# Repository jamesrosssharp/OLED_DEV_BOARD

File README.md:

OLED DEV BOARD
==============

A simple dev board to break out an OLED, PWM sound, buttons, PSRAM
and QSPI flash for making games with iCE40 development boards

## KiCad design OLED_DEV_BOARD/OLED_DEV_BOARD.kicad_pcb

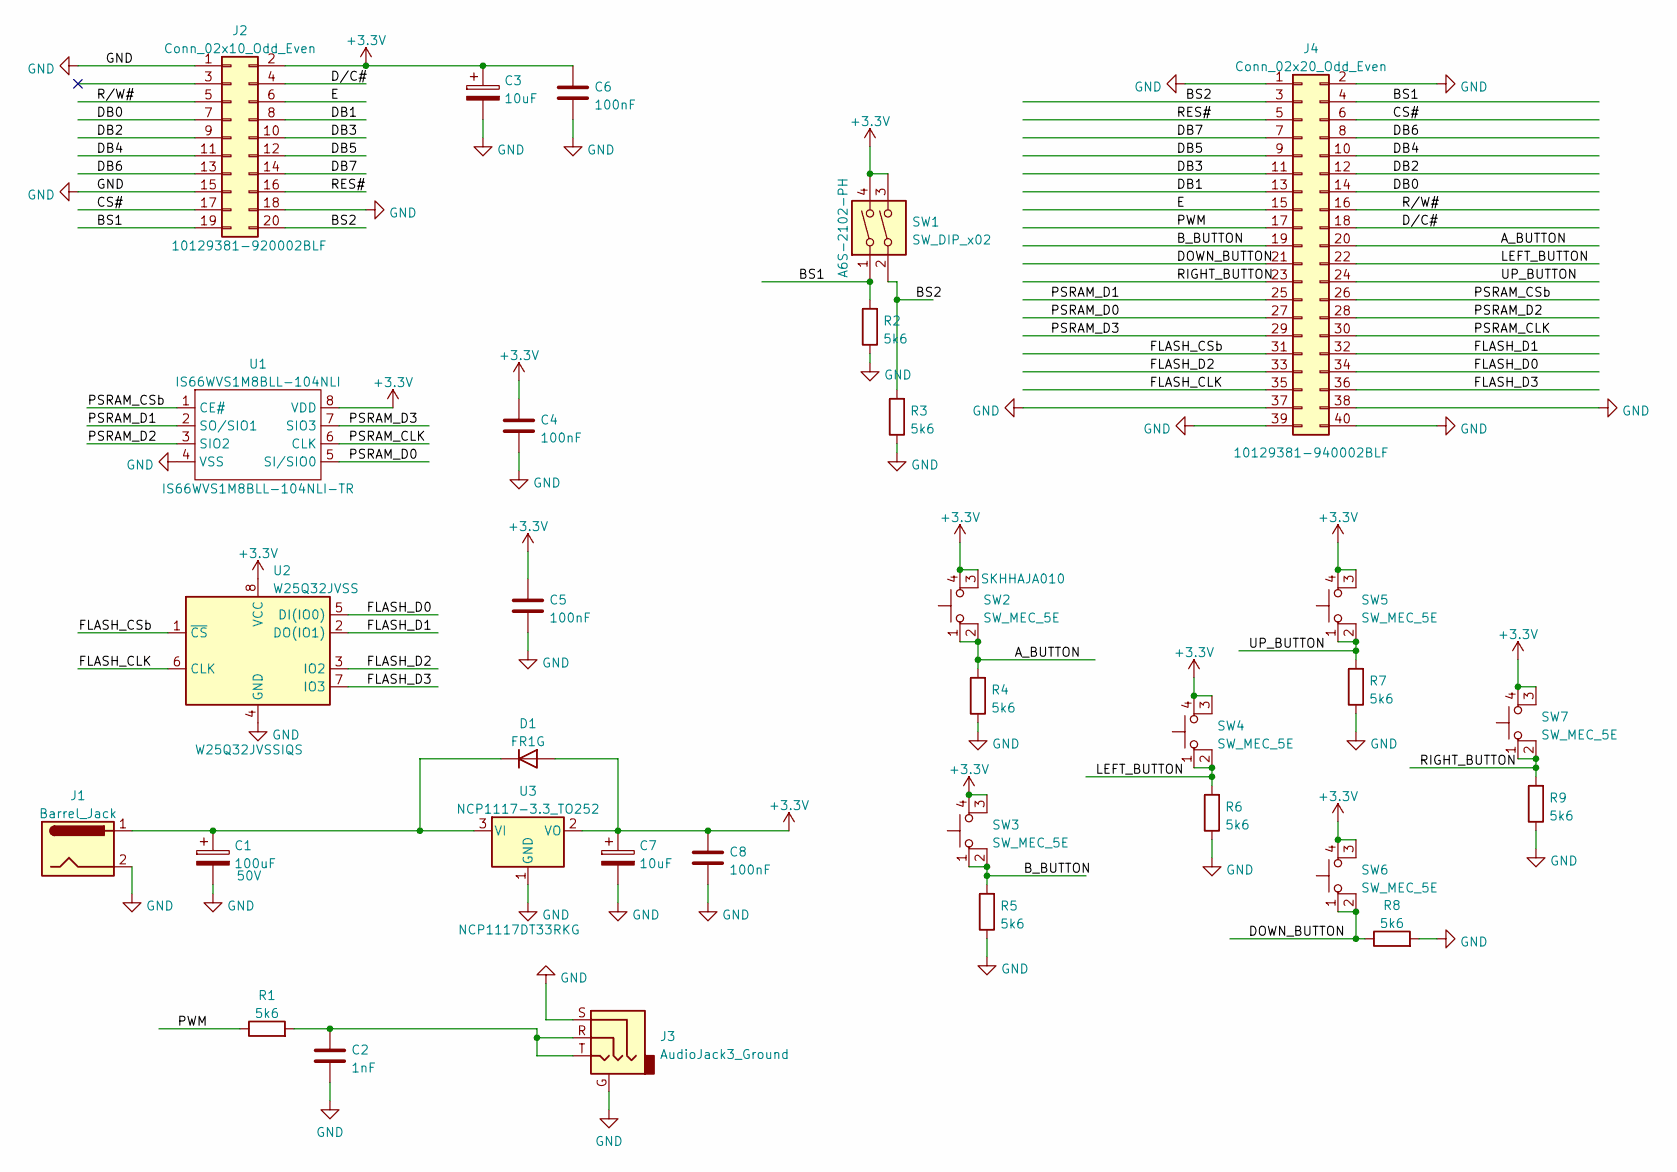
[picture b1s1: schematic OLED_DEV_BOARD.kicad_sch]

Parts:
C1: 100uF; CP_Elec_10x10; Voltage 50V; Manufacturer Part Number GXC1H101MCQ1GS; Mouser Part Number 647-GXC1H101MCQ1GS
C2: 1nF; C_0603_1608Metric; Manufacturer Part Number C0603C102K4RAC7411; Mouser Part Number 80-C0603C102K4RACLR
C3, C7: 10uF; C_1206_3216Metric; Manufacturer Part Number CL31B106KQHNFNE; Mouser Part Number 187-CL31B106KQHNFNE
C4, C5, C6, C8: 100nF; C_0603_1608Metric; Manufacturer Part Number C0603C104K4RACTU; Mouser Part Number 80-C0603C104K4R
D1: FR1G; D_DO-41_SOD81_P10.16mm_Horizontal; Manufacturer Part Number FR1G; Mouser Part Number 637-FR1G
J1: Barrel_Jack; BarrelJack_CUI_PJ-102AH_Horizontal; Manufacturer Part Number PJ-102AH; Mouser Part Number 490-PJ-102AH
J2: Conn_02x10_Odd_Even; NHD-1.8-160128UBC3; Mouser Part Number 649-1012938192002BLF
J3: AudioJack3_Ground; Jack_3.5mm_CUI_SJ-3523-SMT_Horizontal; MPN SJ-3523-SMT-TR; Mouser Part Number 490-SJ-3523-SMT-TR
J4: Conn_02x20_Odd_Even; PinHeader_2x20_P2.54mm_Vertical; Manufacturer Part Number 10129381-940002BLF; Mouser Part Number 649-1012938194002BLF
R1, R2, R3, R4, R5, R6, R7, R8, R9: 5k6; R_0603_1608Metric; Manufacturer Part Number AC0603FR-075K6L; Mouser Part Number 603-AC0603FR-075K6L
SW1: SW_DIP_x02; SW_DIP_SPSTx02_Slide_Omron_A6S-210x_W8.9mm_P2.54mm; Manufacturer Part Number A6S-2102-PH; Mouser Part Number 653-A6S-2102-PH
SW2, SW3, SW4, SW5, SW6, SW7: SW_MEC_5E; SKHHAJA010; Manufacturer Part Number SKHHAJA010; Mouser Part Number 688-SKHHAJ
U1: IS66WVS1M8BLL-104NLI; SOIC-8_5.23x5.23mm_P1.27mm; Manufacturer Part Number IS66WVS1M8BLL-104NLI-TR; Mouser Part Number 870-WVS1M8BLL104NLIT
U2: W25Q32JVSS; SOIC-8_5.23x5.23mm_P1.27mm; Manufacturer Part Number W25Q32JVSSIQS; Mouser Part Number 454-W25Q32JVSSIQS
U3: NCP1117-3.3_TO252; TO-252-2; Manufacturer Part Number NCP1117DT33RKG; Mouser Part Number 863-NCP1117DT33RKG

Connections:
+3V3: C3.1, C4.1, C5.1, C6.1, C7.1, C8.1, D1.2 (A), J2.2, SW1.3, SW1.4, SW2.3 (K), SW2.4 (A), SW3.3 (K), SW3.4 (A), SW4.3 (K), SW4.4 (A), SW5.3 (K), SW5.4 (A), SW6.3 (K), SW6.4 (A), SW7.3 (K), SW7.4 (A), U1.8 (VDD), U2.8 (VCC), U3.2 (VO)
/A_BUTTON: J4.20, R4.2, SW2.1, SW2.2
/BS1: J2.19, J4.4, R2.2, SW1.1
/BS2: J2.20, J4.3, R3.2, SW1.2
/B_BUTTON: J4.19, R5.2, SW3.1, SW3.2
/CS#: J2.17, J4.6
/DB0: J2.7, J4.14
/DB1: J2.8, J4.13
/DB2: J2.9, J4.12
/DB3: J2.10, J4.11
/DB4: J2.11, J4.10
/DB5: J2.12, J4.9
/DB6: J2.13, J4.8
/DB7: J2.14, J4.7
/DOWN_BUTTON: J4.21, R8.1, SW6.1, SW6.2
/D/C#: J2.4, J4.18
/E: J2.6, J4.15
/FLASH_CLK: J4.35, U2.6 (CLK)
/FLASH_CSb: J4.31, U2.1 (~CS)
/FLASH_D0: J4.34, U2.5 (DI(IO0))
/FLASH_D1: J4.32, U2.2 (DO(IO1))
/FLASH_D2: J4.33, U2.3 (IO2)
/FLASH_D3: J4.36, U2.7 (IO3)
/LEFT_BUTTON: J4.22, R6.2, SW4.1, SW4.2
/PSRAM_CLK: J4.30, U1.6 (CLK)
/PSRAM_CSb: J4.26, U1.1 (CE#)
/PSRAM_D0: J4.27, U1.5 (SI/SIO0)
/PSRAM_D1: J4.25, U1.2 (SO/SIO1)
/PSRAM_D2: J4.28, U1.3 (SIO2)
/PSRAM_D3: J4.29, U1.7 (SIO3)
/PWM: J4.17, R1.1
/RES#: J2.16, J4.5
/RIGHT_BUTTON: J4.23, R9.2, SW7.1, SW7.2
/R/W#: J2.5, J4.16
/UP_BUTTON: J4.24, R7.2, SW5.1, SW5.2
GND: C1.2, C2.2, C3.2, C4.2, C5.2, C6.2, C7.2, C8.2, J1.2, J2.1, J2.15, J2.18, J3.G, J3.S, J4.1, J4.2, J4.37, J4.38, J4.39, J4.40, R2.1, R3.1, R4.1, R5.1, R6.1, R7.1, R8.2, R9.1, U1.4 (VSS), U2.4 (GND), U3.1 (GND)
unnamed: C1.1, D1.1 (K), J1.1, U3.3 (VI)
unnamed: C2.1, J3.R, J3.T, R1.2

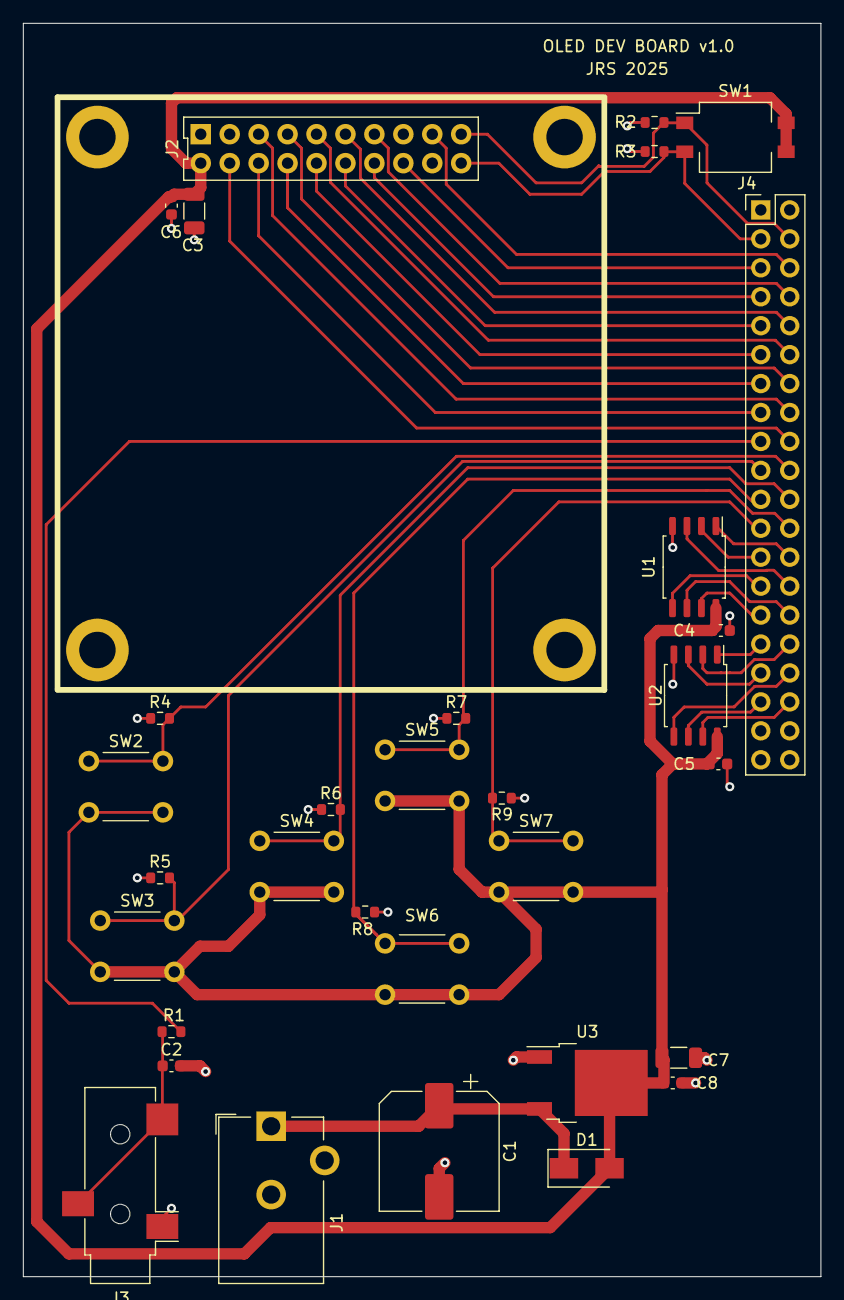
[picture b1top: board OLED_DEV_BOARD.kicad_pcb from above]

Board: 2 copper layers, 70.0 x 110.0 mm, 32 parts (0 on the bottom side), 38 nets.

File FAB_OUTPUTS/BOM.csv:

Ref,Value,Footprint,Datasheet,MPN,MOUSER,,
C5,100nF,Capacitor_SMD:C_0603_1608Metric,,C0603C104K4RACTU,80-C0603C104K4R,,
C6,100nF,Capacitor_SMD:C_0603_1608Metric,,C0603C104K4RACTU,80-C0603C104K4R,,
C7,10uF,Capacitor_SMD:C_1206_3216Metric,,CL31B106KQHNFNE,187-CL31B106KQHNFNE,,
C8,100nF,Capacitor_SMD:C_0603_1608Metric,,C0603C104K4RACTU,80-C0603C104K4R,,
D1,FR1G,Diode_THT:D_DO-41_SOD81_P10.16mm_Horizontal,http://www.vishay.com/docs/88503/1n4001.pdf,FR1G,637-FR1G,,
J1,Barrel_Jack,Connector_BarrelJack:BarrelJack_CUI_PJ-102AH_Horizontal,,PJ-102AH,490-PJ-102AH,,
J2,Conn_02x10_Odd_Even,OLED:NHD-1.8-160128UBC3,,10129381-920002BLF,649-1012938192002BLF,,
J3,AudioJack3_Ground,Connector_Audio:Jack_3.5mm_CUI_SJ-3523-SMT_Horizontal,,SJ-3523-SMT-TR,490-SJ-3523-SMT-TR,,SJ-3523-SMT-TR 
J4,Conn_02x20_Odd_Even,Connector_PinHeader_2.54mm:PinHeader_2x20_P2.54mm_Vertical,,10129381-940002BLF,649-1012938194002BLF,,
R1,5k6,Resistor_SMD:R_0603_1608Metric,,AC0603FR-075K6L,603-AC0603FR-075K6L,,
R2,5k6,Resistor_SMD:R_0603_1608Metric,,AC0603FR-075K6L,603-AC0603FR-075K6L,,
R3,5k6,Resistor_SMD:R_0603_1608Metric,,AC0603FR-075K6L,603-AC0603FR-075K6L,,
R4,5k6,Resistor_SMD:R_0603_1608Metric,,AC0603FR-075K6L,603-AC0603FR-075K6L,,
R5,5k6,Resistor_SMD:R_0603_1608Metric,,AC0603FR-075K6L,603-AC0603FR-075K6L,,
R6,5k6,Resistor_SMD:R_0603_1608Metric,,AC0603FR-075K6L,603-AC0603FR-075K6L,,
R7,5k6,Resistor_SMD:R_0603_1608Metric,,AC0603FR-075K6L,603-AC0603FR-075K6L,,
R8,5k6,Resistor_SMD:R_0603_1608Metric,,AC0603FR-075K6L,603-AC0603FR-075K6L,,
R9,5k6,Resistor_SMD:R_0603_1608Metric,,AC0603FR-075K6L,603-AC0603FR-075K6L,,
SW1,SW_DIP_x02,Button_Switch_SMD:SW_DIP_SPSTx02_Slide_Omron_A6S-210x_W8.9mm_P2.54mm,,A6S-2102-PH,653-A6S-2102-PH,,
SW2,SW_MEC_5E,OLED:SKHHAJA010,http://www.apem.com/int/index.php?controller=attachment&id_a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,SKHHAJA010,688-SKHHAJ,,
SW3,SW_MEC_5E,OLED:SKHHAJA010,http://www.apem.com/int/index.php?controller=attachment&id_a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,SKHHAJA010,688-SKHHAJ,,
SW4,SW_MEC_5E,OLED:SKHHAJA010,http://www.apem.com/int/index.php?controller=attachment&id_a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,SKHHAJA010,688-SKHHAJ,,
SW5,SW_MEC_5E,OLED:SKHHAJA010,http://www.apem.com/int/index.php?controller=attachment&id_a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,SKHHAJA010,688-SKHHAJ,,
SW6,SW_MEC_5E,OLED:SKHHAJA010,http://www.apem.com/int/index.php?controller=attachment&id_a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,SKHHAJA010,688-SKHHAJ,,
SW7,SW_MEC_5E,OLED:SKHHAJA010,http://www.apem.com/int/index.php?controller=attachment&id_a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,SKHHAJA010,688-SKHHAJ,,
U1,IS66WVS1M8BLL-104NLI,Package_SO:SOIC-8_5.23x5.23mm_P1.27mm,,IS66WVS1M8BLL-104NLI-TR,870-WVS1M8BLL104NLIT,,
U2,W25Q32JVSS,Package_SO:SOIC-8_5.23x5.23mm_P1.27mm,http://www.winbond.com/resource-files/w25q32jv%20revg%200327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,W25Q32JVSSIQS,454-W25Q32JVSSIQS,,
U3,NCP1117-3.3_TO252,Package_TO_SOT_SMD:TO-252-2,http://www.onsemi.com/pub_link/Collateral/NCP1117-D.PDF,NCP1117DT33RKG,863-NCP1117DT33RKG,,

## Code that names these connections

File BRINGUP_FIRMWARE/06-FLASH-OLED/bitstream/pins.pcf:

set_io CLK12	35

# 4A
set_io UP_BUTTON 48

# 23B
set_io DOWN_BUTTON 21

# 9B
set_io LEFT_BUTTON 3

# 24A
set_io RIGHT_BUTTON 13

# 8A
set_io A_BUTTON 4

# 22A
set_io B_BUTTON 12

# 25B_G3
set_io OLED_RESb	20

# 5B
set_io OLED_CSb		45

# 29B
set_io OLED_DB[7]	19

# 2A
set_io OLED_DB[6]	47

# 31B
set_io OLED_DB[5]	18

# 3B_G6
set_io OLED_DB[4]	44

# 20A
set_io OLED_DB[3]       11

# 0A
set_io OLED_DB[2]       46

# 18A
set_io OLED_DB[1]	10

# 6A
set_io OLED_DB[0]	2

# 16A
set_io OLED_E		9			

# 13B
set_io OLED_RWb		6

# 49A
set_io OLED_DCb		43


# 44B
set_io FLASH_CSb	34

# 42B
set_io FLASH_D1		31

# 43A
set_io FLASH_D2		32

# 38B
set_io FLASH_D0		27

# 39A
set_io FLASH_D3			26

# 45A_G1
set_io FLASH_SCK		37

set_io SCK	15
# Master (PC) to slave (iCE)
set_io MOSI	17
# Slave (iCE) to master (PC)
set_io MISO	14
set_io CSb 	16


set_io RGB0 39
set_io RGB1 40
set_io RGB2 41

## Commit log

2025-01-12 Added some parts
2025-01-12 Added switches
2025-01-12 Added signals to connector
2025-01-13 Added part number to header
2025-01-14 Added part numbers and footprints
2025-01-14 Added proper footprint for OLED module and placed components roughly
2025-01-16 Made board smaller
2025-01-17 Changed ordering of pins for display so it would route better
2025-01-17 Mostly routed
2025-01-19 Added Fab Outputs
2025-01-19 Committed changes
2025-01-19 Added BOM
2025-02-01 Added some test firmware
2025-02-01 Added OLED test
2025-02-02 Added OLED test in FPGA
2025-02-02 Finish better OLED test
2025-02-02 Added flash test
2025-02-03 Added audio test
2025-04-25 Added start of firmware to stream from flash to OLED
2025-05-04 Added start of flash streaming
